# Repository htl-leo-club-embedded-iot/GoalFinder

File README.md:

# Goalfinder

## About

The GoalFinder device aims to help blind or visually impaired people play basketball by playing a sound to help locate the basket and provides acoustic and visual feedback on hits and misses.
For more information, please visit the [GoalFinder Website](https://goalfinder.github.io)

## Branches

### Main Branches

+ `main` The main branch is used for releases only
+ `development` Is the branch that sees all development work

### Backup Branches

There are still two discontinued branches from before the takeover

+ `pages-alt` Old GitHub Pages branch
+ `multithreading-alt` Old branch focused on adding multithreading to the GoalFinder device

## Website

The GoalFinder website is accessible at [goalfinder.github.io](https://goalfinder.github.io) and is split of into [it's own repository](https://github.com/goalfinder/goalfinder.github.io)

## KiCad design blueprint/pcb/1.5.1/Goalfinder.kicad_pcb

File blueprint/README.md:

# Blueprint Directory

## Structure
    .
    ├── design          The development section for the GoalFinder device
    │   ├── housing/        The design for the housing
    │   └── pcb/            The design for the PCB
    └── export          To be exported files for production
        ├── 3d-files/       .3mf projects or .gcode (mostly for Creality K1C and K1 Max printers using Hyper-PLA) files for producing the housing
        └── pcb/            Generated production files for producing the PCB

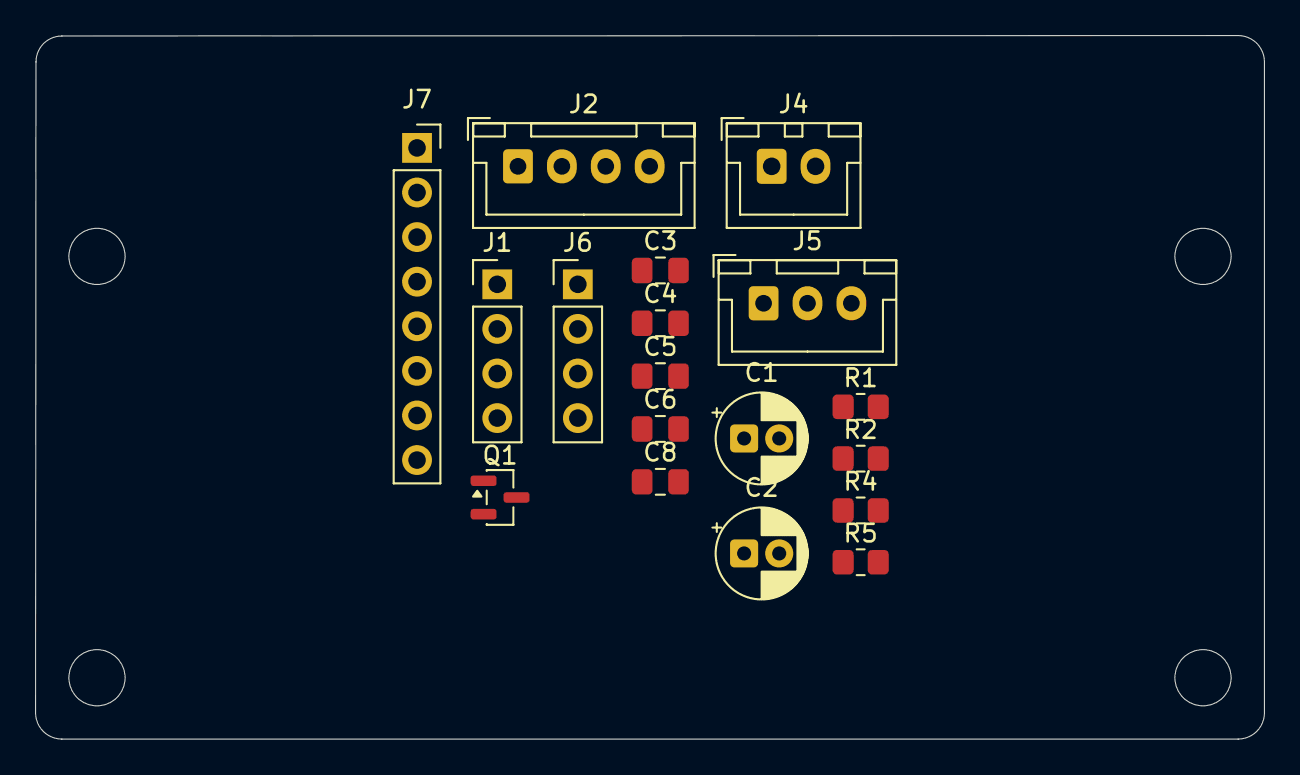
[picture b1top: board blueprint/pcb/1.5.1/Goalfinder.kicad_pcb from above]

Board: 2 copper layers, 70.0 x 40.1 mm, 22 parts (0 on the bottom side), 7 nets, no tracks yet.

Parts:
C1: 22µF; CP_Radial_D5.0mm_P2.00mm
C2: 4,7µF; CP_Radial_D5.0mm_P2.00mm
C3, C4, C5, C6, C8: 100nF; C_0805_2012Metric_Pad1.18x1.45mm_HandSolder
J1: USB in; PinHeader_1x04_P2.54mm_Vertical
J2: USB-ESP; JST_XH_B4B-XH-A_1x04_P2.50mm_Vertical
J4: LED Strip; JST_XH_B2B-XH-A_1x02_P2.50mm_Vertical
J5: SW240 - Vcc/D0/GND; JST_XH_B3B-XH-A_1x03_P2.50mm_Vertical
J6: VL53L0X-ToF Vcc/SDA/SCL/GND; PinHeader_1x04_P2.54mm_Vertical
J7: Conn_01x08_Pin; PinSocket_1x08_P2.54mm_Vertical
MH1, MH2, MH3, MH4: MountingHole_3.2mm_M3
Q1: IRLML2502; SOT-23
R1, R2: 100k; R_0805_2012Metric_Pad1.20x1.40mm_HandSolder
R4: 1k; R_0805_2012Metric_Pad1.20x1.40mm_HandSolder
R5: 33k; R_0805_2012Metric_Pad1.20x1.40mm_HandSolder

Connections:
3V3: C5.1, C6.1, C8.1, J5.1, J6.1, J7.1
5V: C1.1, C2.1, C3.1, C4.1, J1.1, J2.1, J4.1, R1.1
/LED_PWR: J4.2, Q1.3 (D)
GND: C1.2, C2.2, C3.2, C4.2, C5.2, C6.2, C8.2, J1.4, J2.4, J5.3, J6.4, J7.2, Q1.2 (S), R2.1, R5.2
unnamed: J1.2, J2.2
unnamed: J1.3, J2.3
unnamed: Q1.1 (G), R4.2, R5.1

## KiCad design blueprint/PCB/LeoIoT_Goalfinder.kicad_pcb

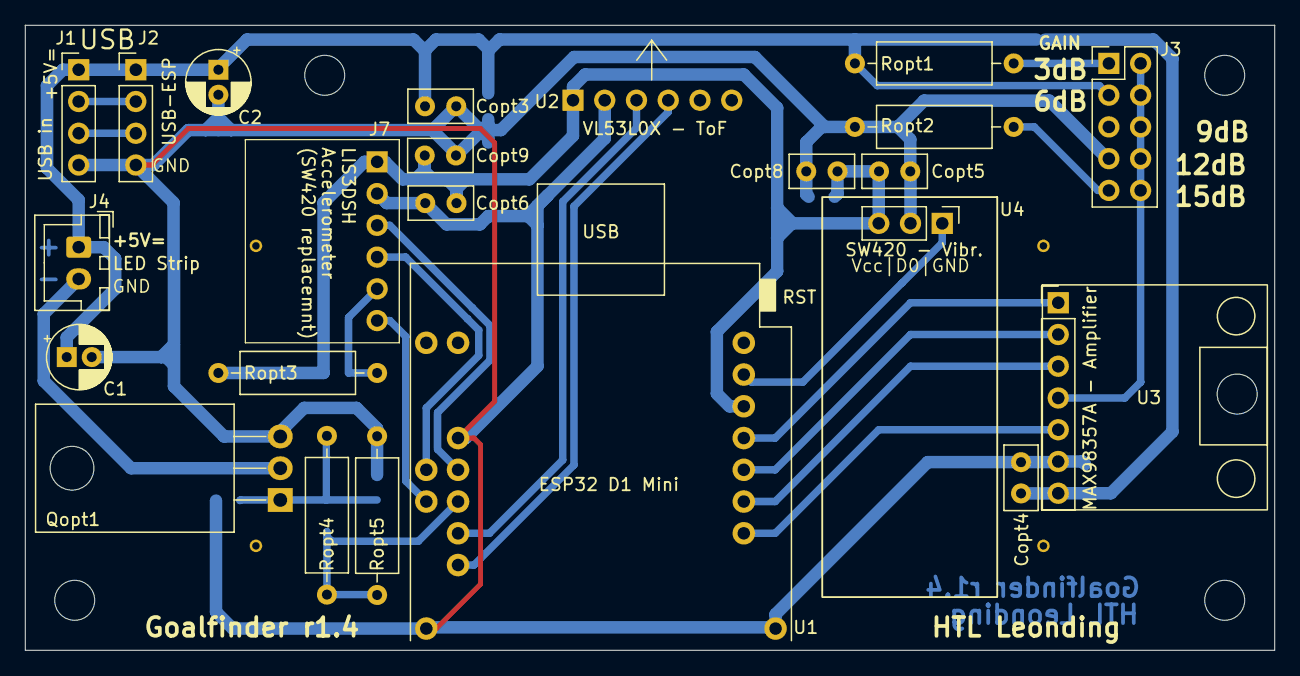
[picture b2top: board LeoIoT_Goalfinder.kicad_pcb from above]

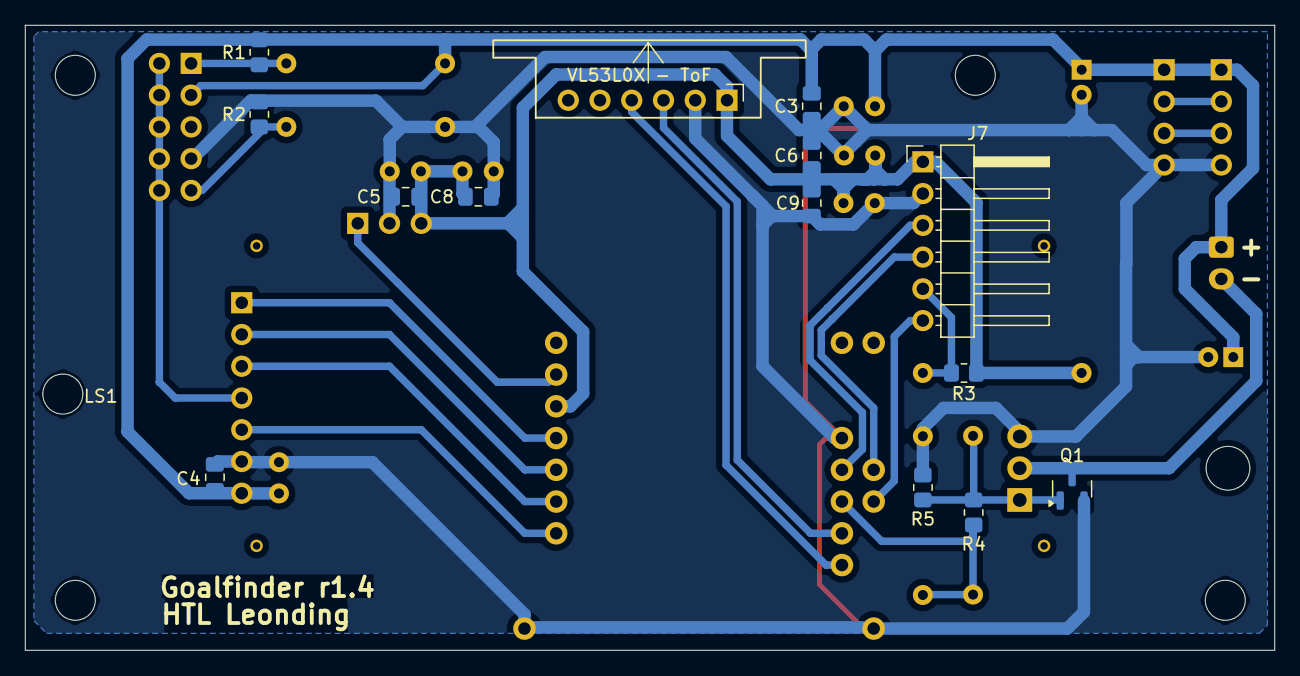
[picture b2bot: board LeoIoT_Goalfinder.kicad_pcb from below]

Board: 2 copper layers, 100.0 x 50.0 mm, 41 parts (15 on the bottom side), 22 nets.

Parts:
C1: 22µF; CP_Radial_D5.0mm_P2.00mm
C2: 4,7µF; CP_Radial_D5.0mm_P2.00mm
C3, C4, C5, C6, C8, C9: 100nF; C_0805_2012Metric_Pad1.18x1.45mm_HandSolder
Copt3, Copt4, Copt5, Copt6, Copt8, Copt9: 100nF; C_Disc_D5.0mm_W2.5mm_P2.50mm
J1: USB in; PinHeader_1x04_P2.54mm_Vertical
J2: USB-ESP; PinHeader_1x04_P2.54mm_Vertical
J3: GAIN; PinHeader_2x05_P2.54mm_Vertical
J4: LED Strip; JST_XH_B2B-XH-A_1x02_P2.54mm_Vertical
J7: LIS3DH; PinHeader_1x06_P2.54mm_Horizontal
LS1: Speaker; Mono-Enclosed_Speaker_70x30x17mm_onboard
MH1, MH2, MH3, MH3#2, MH4: MountingHole_3.2mm_M3
Q1: IRLML2502; SOT-23
Qopt1: IRLML2502; TO-220-3_Horizontal_TabDown
R1, R2, R3: 100k; R_0805_2012Metric_Pad1.20x1.40mm_HandSolder
R4: 1k; R_0805_2012Metric_Pad1.20x1.40mm_HandSolder
R5: 33k; R_0805_2012Metric_Pad1.20x1.40mm_HandSolder
Ropt1, Ropt2, Ropt3: 100k; R_Axial_DIN0309_L9.0mm_D3.2mm_P12.70mm_Horizontal
Ropt4: 1k; R_Axial_DIN0309_L9.0mm_D3.2mm_P12.70mm_Horizontal
Ropt5: 33k; R_Axial_DIN0309_L9.0mm_D3.2mm_P12.70mm_Horizontal
U1: ESP32 D1 Mini; ESP32_D1_mini
U2: VL53L0X - ToF; VL53L0X_Breakout_Board_vertical_flat
U3: MAX98357A - Amplifier; MAX98357A_Breakout_Board
U4: SW240 - Vcc/D0/GND; SW420_Breakout_Board_Horizontal

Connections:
3V3: C5.1, C6.1, C8.1, C9.1, Copt5.1, Copt6.1, Copt8.1, Copt9.1, J7.1, R3.1, Ropt3.1, U1.16 (3V3), U2.1 (VCC), U4.3
5V: C1.1, C2.1, C3.1, C4.1, Copt3.1, Copt4.1, J1.1, J2.1, J3.3, J4.1, R1.1, Ropt1.1, U3.7 (VDD)
/LED_PWR: J4.2, Q1.3 (D), Qopt1.2 (S)
GND: C1.2, C2.2, C3.2, C4.2, C5.2, C6.2, C8.2, C9.2, Copt3.2, Copt4.2, Copt5.2, Copt6.2, Copt8.2, Copt9.2, J1.4, J2.4, J3.7, J7.2, Q1.2 (S), Qopt1.3 (D), R2.1, R5.2, Ropt2.1, Ropt5.2, U1.1 (GND), U1.22 (GND), U1.33 (GND), U2.2 (GND), U3.6 (GND), U4.2
unnamed: J1.2, J2.2
unnamed: J1.3, J2.3
unnamed: J3.1, R1.2, Ropt1.2
unnamed: J3.9, R2.2, Ropt2.2
unnamed: U1.18 (IO_13/TCK), U4.1
unnamed: U1.27 (IO_21/SDA_1), U2.3 (SDA)
unnamed: U1.25 (IO_22/SCL_1), U2.4 (SCL)
unnamed: J7.3, U1.31 (IO_16/U2_RX)
unnamed: J7.4, U1.32 (IO_04)
unnamed: J7.5, R3.2, Ropt3.2
unnamed: J7.6, U1.30 (IO_12/TDI)
unnamed: Q1.1 (G), Qopt1.1 (G), R4.2, R5.1, Ropt4.2
unnamed: U1.14 (IO_05/SS), U3.1 (LRCLK)
unnamed: R4.1, Ropt4.1, Ropt5.1, U1.29 (IO_17/U2_TXC)
unnamed: U1.8 (IO_18/CLK), U3.5 (~SD_MODE)
unnamed: U1.10 (IO_19/MISO), U3.3 (DIN)
unnamed: U1.12 (IO_23/MOSI), U3.2 (BCLK)
unnamed: J3.2, J3.4, J3.6, J3.8, J3.10, U3.4 (GAIN_SLOT)

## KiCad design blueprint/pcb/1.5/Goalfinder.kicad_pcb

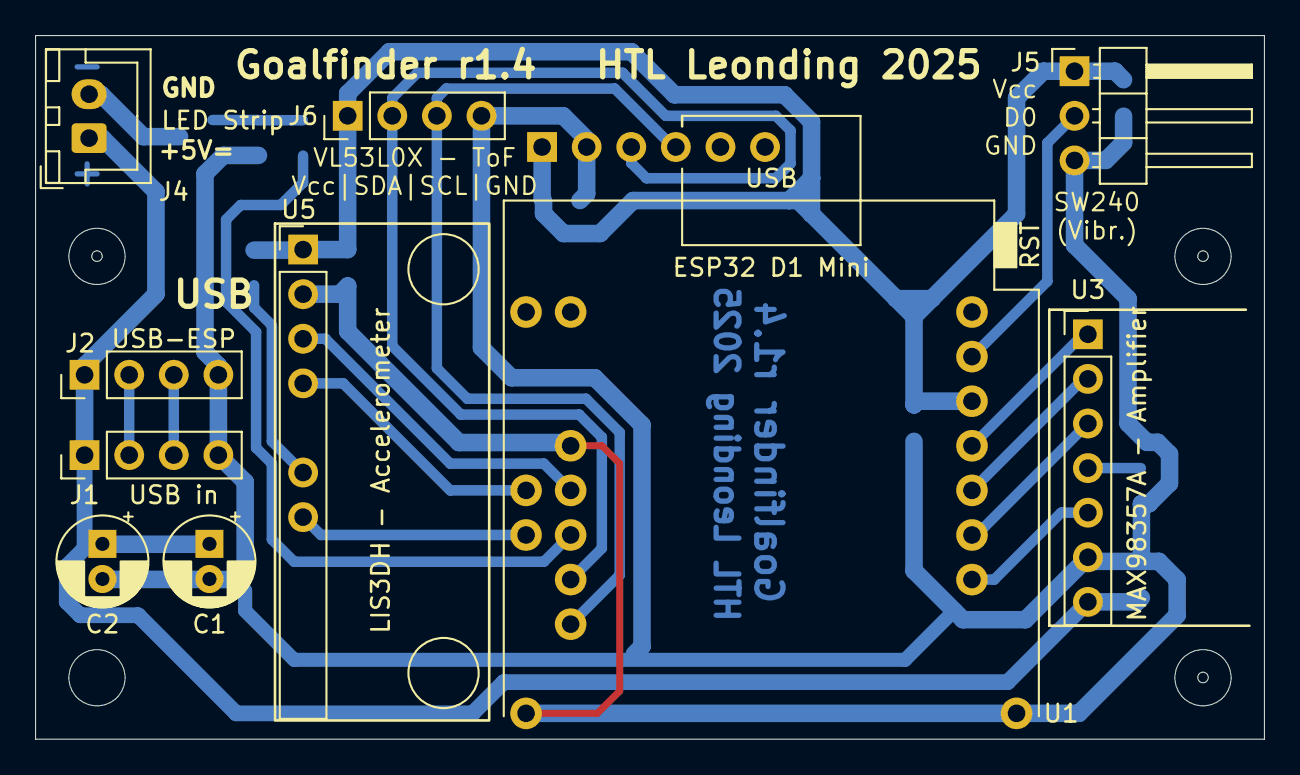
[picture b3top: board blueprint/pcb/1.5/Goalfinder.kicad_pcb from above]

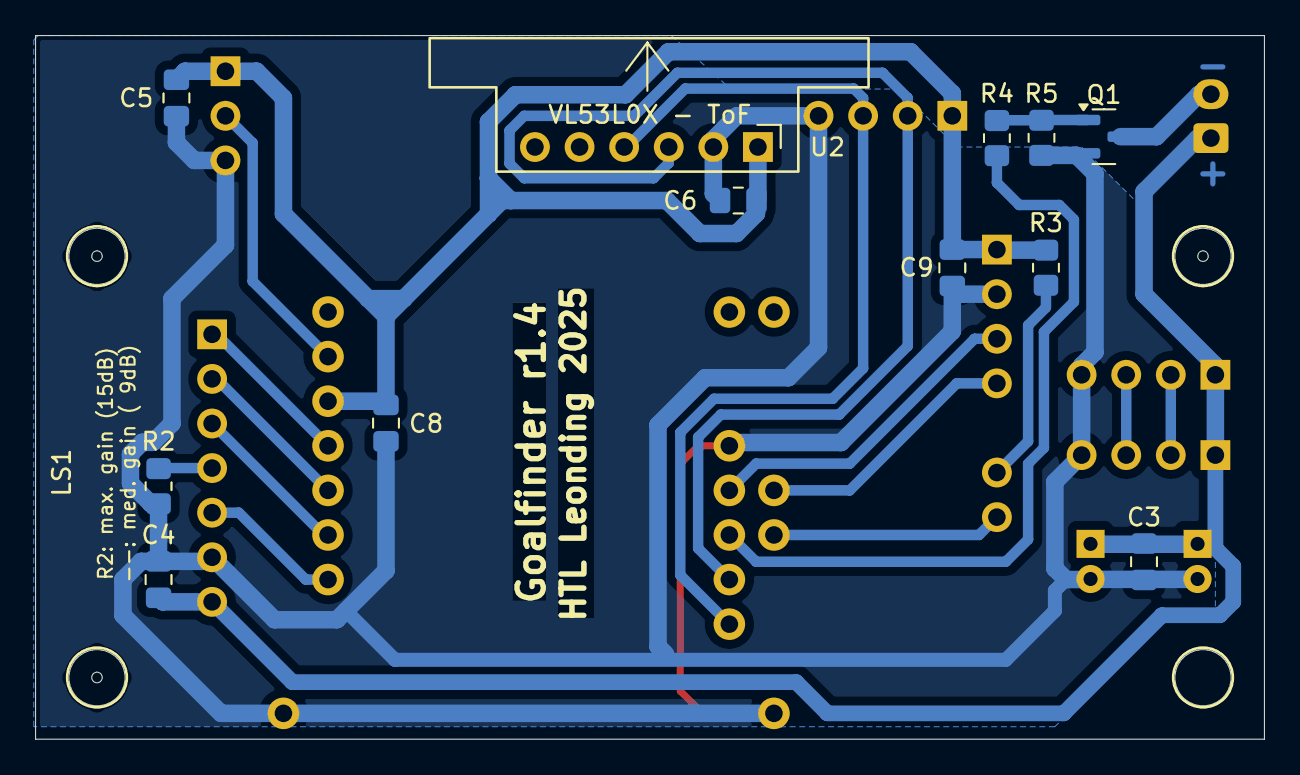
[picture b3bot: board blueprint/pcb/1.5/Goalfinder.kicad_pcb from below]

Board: 2 copper layers, 70.0 x 40.1 mm, 27 parts (13 on the bottom side), 20 nets.

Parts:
C1: 22µF; CP_Radial_D5.0mm_P2.00mm
C2: 4,7µF; CP_Radial_D5.0mm_P2.00mm
C3, C4, C5, C6, C8, C9: 100nF; C_0805_2012Metric_Pad1.18x1.45mm_HandSolder
J1: USB in; PinHeader_1x04_P2.54mm_Vertical
J2: USB-ESP; PinHeader_1x04_P2.54mm_Vertical
J4: LED Strip; JST_XH_B2B-XH-A_1x02_P2.50mm_Vertical
J5: SW240 - Vcc/D0/GND; PinHeader_1x03_P2.54mm_Horizontal
J6: VL53L0X-ToF Vcc/SDA/SCL/GND; PinHeader_1x04_P2.54mm_Vertical
LS1: Speaker; Mono-Enclosed_Speaker_70x30x17mm_onboard
MH1, MH2, MH3, MH4: MountingHole_3.2mm_M3
Q1: IRLML2502; SOT-23
R2, R3: 100k; R_0805_2012Metric_Pad1.20x1.40mm_HandSolder
R4: 1k; R_0805_2012Metric_Pad1.20x1.40mm_HandSolder
R5: 33k; R_0805_2012Metric_Pad1.20x1.40mm_HandSolder
U1: ESP32 D1 Mini; ESP32_D1_mini
U2: VL53L0X - ToF; VL53L0X_Breakout_Board_vertical_flat
U3: MAX98357A - Amplifier; MAX98357A_Breakout_Board
U5: LIS3DH - Accelerometer; LIS3DH_Breakout_Board

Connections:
3V3: C5.1, C6.1, C8.1, C9.1, J5.1, J6.1, R3.1, U1.16 (3V3), U2.1 (VCC), U5.1 (VCC)
5V: C1.1, C2.1, C3.1, C4.1, J1.1, J2.1, J4.1, U3.7 (VDD)
/LED_PWR: J4.2, Q1.3 (D)
GND: C1.2, C2.2, C3.2, C4.2, C5.2, C6.2, C8.2, C9.2, J1.4, J2.4, J5.3, J6.4, Q1.2 (S), R2.1, R5.2, U1.1 (GND), U1.22 (GND), U1.33 (GND), U2.2 (GND), U3.6 (GND), U5.2 (GND)
unnamed: J1.2, J2.2
unnamed: J1.3, J2.3
unnamed: J5.2, U1.18 (IO_13/TCK)
unnamed: J6.2, U1.27 (IO_21/SDA_1), U2.3 (SDA)
unnamed: J6.3, U1.25 (IO_22/SCL_1), U2.4 (SCL)
unnamed: U1.31 (IO_16/U2_RX), U5.3 (SCL/SPC)
unnamed: U1.32 (IO_04), U5.4 (SDA/SDI/SDO)
unnamed: R3.2, U5.6 (CS)
unnamed: U1.30 (IO_12/TDI), U5.7 (INT1)
unnamed: Q1.1 (G), R4.2, R5.1
unnamed: U1.14 (IO_05/SS), U3.1 (LRCLK)
unnamed: R4.1, U1.29 (IO_17/U2_TXC)
unnamed: U1.8 (IO_18/CLK), U3.5 (~SD_MODE)
unnamed: U1.10 (IO_19/MISO), U3.3 (DIN)
unnamed: U1.12 (IO_23/MOSI), U3.2 (BCLK)
unnamed: R2.2, U3.4 (GAIN_SLOT)

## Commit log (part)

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2025-10-20 fixed
2025-12-24 Renamed assets folder
2025-12-24 Restructured folders
2025-12-24 Sorted .stl files
2025-12-25 Reworked blueprint/ structure
2025-12-25 Structured blueprint main model working hirarchy
2025-12-25 Reworked Schematic to use MPU6050
2025-12-26 Resolved path issues in web/
2025-12-26 Added documentation template for web/usage/ and updated general doc
2025-12-28 Added initial technical documentation
2025-12-28 Restructured documentation
2025-12-28 Added contribution documentation
2025-12-28 Added documentation on tags
2026-01-09 Modify README.md
2026-01-26 Added #9 & updated paths in main.yml
2026-01-27 Implement #54
2026-01-27 Revert "Initial fix on player skip not registering #52"
2026-02-08 Fixed mutex for audio playback
2026-02-09 added high_res and low_res assembly photos
2026-02-10 Fix browser reload causing file download on iOS\n\nSet content type to text/html when falling back to index.html for SPA\nroutes. Previously the content type was empty for extensionless routes\nlike 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
2026-02-10 Add captive portal for auto browser open on WiFi connect\n\nAdd DNS server that redirects all domain lookups to the AP IP, plus\ncaptive portal detection endpoints for Android, iOS/macOS, Windows,\na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
2026-02-10 Fixed Software-Over-The-Air #8
2026-02-11 Added new contributors to web app, fixed typos & reworked comments
2026-02-11 Added images to docs/
2026-02-11 Ran build to apply new web to firmware
2026-02-11 Added optimization of uploadfs
2026-02-12 Added handling of image file extensions #75
2026-02-12 Fixed Spacing on Embeded Website
2026-02-12 Removed unused code WifiManager.h and WifiManager.cpp
2026-02-12 Add first run setting #77
2026-02-12 Moved WiFi setup in GoalfinderApp.cpp #77
2026-02-12 Implement scanning for other GoalFinder devices #77
2026-02-12 Improved comments in Goalfinderapp.h
2026-02-12 Fixed Hit/Miss buttons not working properly
2026-02-12 Fixed Zeitspiel-Challange: Buttons
2026-02-12 Added width & height tags to svg image, for it to work on safari browser engine
2026-02-12 Added feature, so get requests for hit/miss will stop after a game has ended
2026-02-13 Remove compressed index to resolve merge conflicts #86
2026-02-13 Update README to remove contribution and version info
    Removed contributing guidelines and version management details from README.
2026-02-13 Added fresh build of the web app
2026-02-13 Added header in Web App #82
2026-02-13 Added headers #82
2026-02-14 Improved core binding for crutial tasks #3
2026-02-14 Improved audio settings interface #95
2026-02-14 Initial improvment of System settings #95
2026-02-14 Improved styling unity for audio settings #72
2026-02-14 Improved styling unity for LED settings #72
2026-02-14 Improved styling unity for system settings #72
2026-02-14 Simplified style for settings #72
2026-02-14 Improved percentage settings #95
2026-02-14 Added proper clamping of values for settings #72
2026-02-14 Improved About page #72
2026-02-14 Improved Home page #72
2026-02-14 Improved Games pages #72
2026-02-14 Added accent color selection #99
2026-02-14 Implement settings for #100 & #101
2026-02-14 Added translation for Games #102
2026-02-14 Added not connected modal
2026-02-14 Added device side auth handling #103
2026-02-14 Added client side auth #103
2026-02-17 Applied restructuring of WiFi setup
2026-02-17 Readded client side handling of WiFi password protection
2026-02-17 Added Web App input form for WiFi password #106
2026-02-18 Refactor update-version.py #114
2026-02-18 General cleanup of root direcoty
2026-02-18 Resolve build issue
2026-02-18 Resolve web app build issues
2026-02-19 Move part of README.md to documentation
2026-02-19 Implement new setting category #125
2026-02-19 Add setting for #98
2026-02-19 Add missing setting in settings.ts #98
2026-02-19 Added device side settings for #98 & #126
2026-02-20 Implement initial distance only reading #126
2026-02-20 Fixed Settings Instance issue and fixed saving of distance only hit detection #126
2026-02-20 Add Contributor Covenant Code of Conduct
    Added Contributor Covenant Code of Conduct to outline community standards and enforcement.
2026-02-20 Revise security policy for clarity and conciseness
    Updated the security policy to simplify supported versions and reporting process.
2026-02-20 Fixes for #123, #128 & other minor issues
2026-02-20 Added favicon #127
2026-02-20 Implement Free Play game mode #108
2026-02-20 Update release notes
2026-02-21 Fix #132
2026-02-21 Implement basic functionality for #91
2026-02-21 Improved not connected modal
2026-02-21 Added proper handling of version update in the web app
2026-02-22 Applied fix for #140
2026-02-22 Moved device connection settings into own view and added placeholder restart modal
2026-02-22 Revise CONTRIBUTING.md for clarity and updates
    Removed outdated sections and streamlined contribution guidelines.
2026-02-22 Remove 'Latest Version' section from README
    Removed the 'Latest Version' section from README.md.
2026-02-22 Clarify information about GoalFinder Website
    Updated wording for clarity in the README.
2026-02-23 Add custom logger
2026-02-23 Added functionality for placehodlers in logger
2026-02-23 Implement usage of logger
2026-02-24 Removed unuecesarry comment
2026-02-24 Fixed looping in GoalfinderApp & added missing sound paths in array #147
2026-02-24 Applied further fixes to make detection distance better setable #148
2026-02-26 Added doc on i3 commands
2026-02-27 Added needed classes #96
2026-02-27 Added working example for testing accelerometer shot detection #109
2026-03-01 Added settings for #153 and improved client side password validation
2026-03-01 Experimental implementation of #153
2026-03-01 Fixed security problem with rollup
2026-03-02 Added DNS Server #146
2026-03-02 Implement usage of WebSockets #151 #96
2026-03-03 Fresh webh app build and improved mutex saving
2026-03-03 Formatted lib files
2026-03-03 Finished work on VL53L0X lib
2026-03-03 Finished improvments on SW420
2026-03-03 Reworked fs to be a lib
2026-03-03 Fixed compile time errors for libs
2026-03-17 Removed ununnecessary assets from repository #122
2026-03-20 Added PCB Component 3D models
2026-03-28 Added GoalFinder printing projects
2026-03-28 IMproved consistancy of logging and improved DNS Server code quality
2026-04-02 Reduced interference of web app loading on audio #167
2026-04-02 Fixed web socket not opening on certain devices #170
2026-04-02 Fixed inconsitent LED fading animation #168
2026-04-02 Fix allignment
2026-04-03 Fix page allignment
2026-04-04 Made allignment more conistant across settings
2026-04-04 Added device side settings for #157 & #172
2026-04-04 Added device side settings for #153
2026-04-04 Added option to enable advanced settings #169
2026-04-04 Addded web app side handling of DNS enabling #173
2026-04-04 Added device side handling of DNS disabling #173
2026-04-04 Improved DNS resolving
2026-04-05 Further performance performance #151 #169
2026-04-06 Added option to set timeout between metronome ticks #177
2026-04-06 Improved audio selection #177
2026-04-06 Improved logging and made final tweaks to #177
2026-04-06 Fixed audio for miss-1.mp3 #177
2026-04-06 Improved web app side LED settings #157
2026-04-06 Made flash and turbo LED timing connected to metronome timing #157
2026-04-06 Added simplified controls for sensor sensitivity #157
2026-04-07 Simplified hoop size selection #157
2026-04-07 Add .gitattributes to mark .gcode as generated
2026-04-07 Readd .gitattributes
2026-04-07 Add workflow_dispatch trigger to main.yml
2026-04-07 Remove coverage testing
2026-04-07 Fixed include path
2026-04-10 fix: vulnerability #185
2026-04-11 fix: wrong class: active binding causing #187
2026-04-15 Added setting fields for #175
2026-04-15 add: implementation fo connecting to external networks #175
2026-04-17 rework: wifi password input #175
2026-04-17 revert: undo recent changes made on the wrong branch
2026-04-19 improve: entering password and logic for handling if password is present #175
2026-04-19 refactor: structuring of skill files
2026-04-19 add: TODOs for #192
2026-04-19 add: web app support for manual network configuration #175
2026-04-21 fix: showing device password when advanced settings are disabled
2026-04-21 fix: intial hotfix for #194
2026-04-23 update: version to v0.5.2a
2026-04-24 fix: proper checking for automatic user theme preference #201
2026-04-24 add: timeout to let audio buffer up #201
2026-04-28 remove: dubplicate apply button for enterprise network password #226
2026-04-28 remove: testing stub #205
2026-04-30 fix: setting names being too long
2026-05-03 refactor: device name input #193
2026-05-03 remove: apply button for personal auth external networks
2026-05-03 refactor: improve code quality in HttpServer.cpp
2026-05-03 refactor: improve code quality in WebSocket.cpp
2026-05-03 add: .gitignore
2026-05-03 add: flag setting for web logging #224
2026-05-03 add: sending web log messages from Logger utility
2026-05-03 add: queuing for ws log sending #224
2026-05-04 add: window for displaying log in the web app #224
2026-05-04 refactor: initialization logging
2026-05-04 remove: unnecessary versioning workflows #220
2026-05-04 add: script for #220
2026-05-05 fix: path to update version script
2026-05-05 rename: Version.h to fix update version
2026-05-05 fix: path to Version.h not considering relative position
2026-05-05 fix: using wrong py version in main.yml workflow
2026-05-05 fix: rename file git
2026-05-06 fix: version getting by pattern
2026-05-07 fix: regular expression in update version script
2026-05-13 fix: ip-address security vulnerability
2026-05-16 add: simple encryption of sensitive fields #233
2026-05-16 fix: compile time errors relate to #233
2026-05-18 fix: falsely falling back to no encryption #233
2026-05-18 fix: not running shedule save for #235
2026-05-29 add: propper sensitivity field for SW420 lib
2026-05-29 refactor: SW420 to read changes for LOW not HIGH
2026-05-31 refactor: SW420 library to only read changes in state #210
2026-05-31 add: propper ISR for shot detection #209
2026-05-31 add: basic sunlight protection #215
2026-06-01 rework: volume of all audio files #206
2026-06-02 add: hit reading routine #216
2026-06-07 fix: not recognzing valid readings for VL53L0X #212
2026-06-07 remove: time consuming and inaccurate hit read ISR #214
2026-06-15 add: timeout before playback to let audio buffer
2026-06-15 fix: allignment of manual network config relate to #237
2026-06-15 fix: #238
2026-06-16 fix: security vulnerability #32 #33
2026-06-17 fix: css and redirect error
2026-06-17 add: basic LED feedback #149
2026-06-24 improve: general hit detection
2026-06-24 fix: text alignement #241
2026-06-24 fix: inverted sensitivity setting #240
2026-06-24 fix: reliability when reading hit right after shot event
2026-06-24 improve: general logging
2026-06-24 replace: old text based header buttons with icons and add play pause switching to all affected icons
2026-06-24 fix: captive to redirect to base url and not games panel
2026-06-24 implement: spectating panel #193
2026-06-24 add: proper basket modes #90
2026-06-25 fix: issue with package.json
2026-06-25 fix: node build issue
2026-06-26 adjust: values for hit basket presets
2026-06-27 add: firmware side implementation of #248
2026-06-27 add: game presets #199
2026-06-27 add: game state struct #146
2026-06-30 update: contribution guidelines to match the one existing in the documentation
2026-06-30 update: copyright year in LICENSE
    Updated copyright year in LICENSE file.
2026-06-30 Clarify vulnerability reporting guidelines
    Updated the security policy to clarify reporting procedures.
2026-06-30 add: issue templates
2026-06-30 update: vulnerability reporting instructions in SECURITY.md
2026-06-30 move: directories out of client/
2026-06-30 update: inital PCB design version to 0.1.5
2026-06-30 remove: old GoalFinder PCB export
2026-06-30 move: entire old GoalFinder blueprint files #144
2026-06-30 refactor: PCB files into speerate tof module project and main device project #144
